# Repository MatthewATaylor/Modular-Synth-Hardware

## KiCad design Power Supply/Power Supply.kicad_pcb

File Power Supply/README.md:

# Power Supply

A linear power supply for +12V, -12V, and +5V.

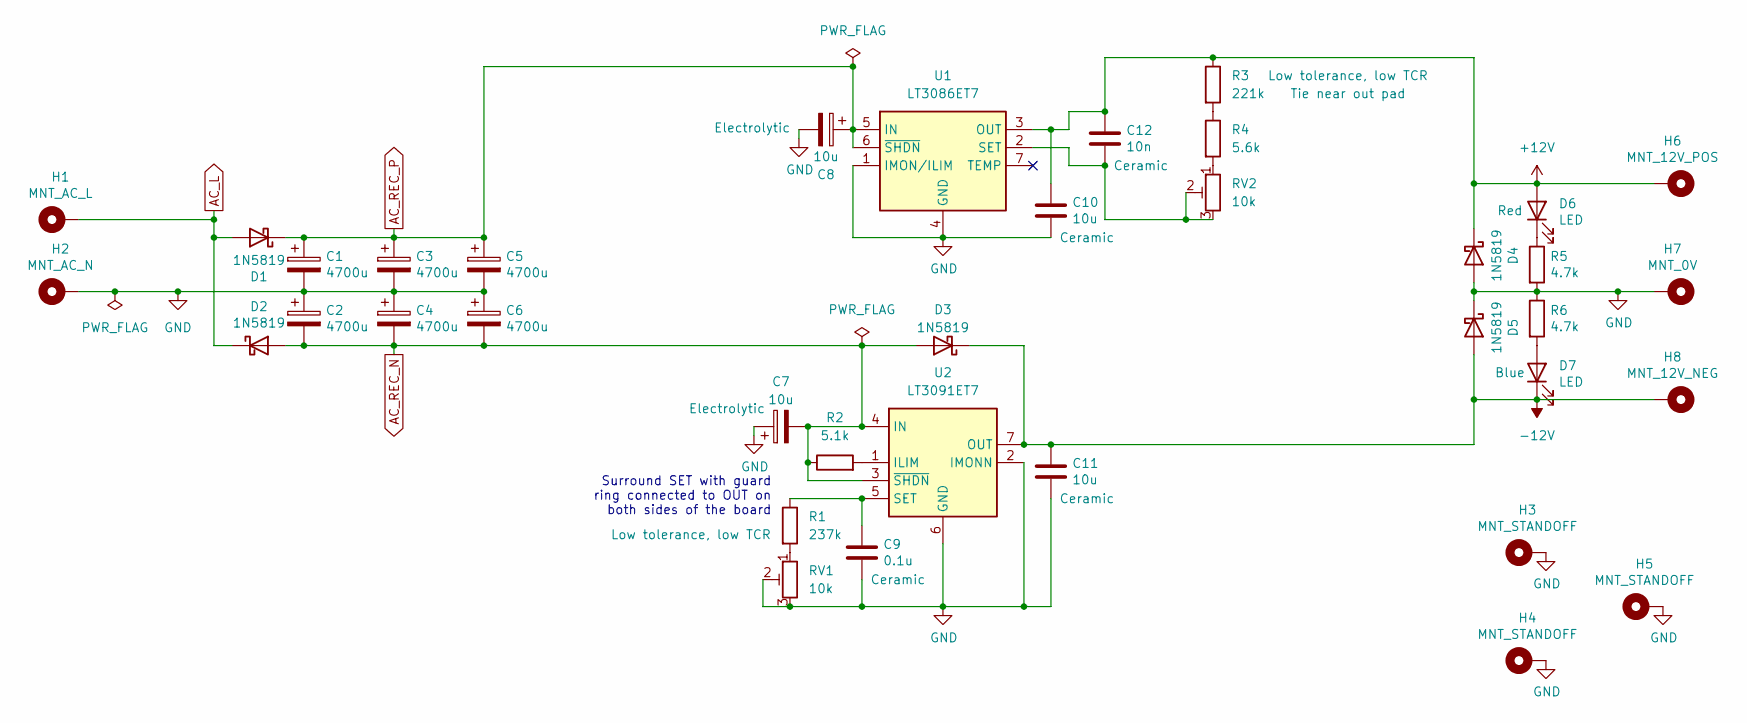
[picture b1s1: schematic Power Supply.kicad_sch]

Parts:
C1, C2, C3, C4, C5, C6: 4700u; CP_Radial_D18.0mm_P7.50mm
C7, C8: 10u; CP_Radial_D5.0mm_P2.50mm
C9: 0.1u; C_Disc_D5.5mm_W2.5mm_P2.50mm
C10, C11: 10u; C_Disc_D5.5mm_W4.0mm_P2.50mm
C12: 10n; C_Disc_D5.5mm_W2.5mm_P2.50mm
D1, D2, D3, D4, D5: 1N5819; D_DO-41_SOD81_P10.16mm_Horizontal
D6, D7: LED; LED_D5.0mm
H1: MNT_AC_L; MountingHole_Pitch1.7mm_Drill1mm
H2: MNT_AC_N; MountingHole_Pitch1.7mm_Drill1mm
H3, H4, H5: MNT_STANDOFF; MountingHole_Pitch7.5mm_Drill3.4mm
H6: MNT_12V_POS; Wuerth_REDCUBE-THR_WP-THRSH_74651195_THR
H7: MNT_0V; Wuerth_REDCUBE-THR_WP-THRSH_74651195_THR
H8: MNT_12V_NEG; Wuerth_REDCUBE-THR_WP-THRSH_74651195_THR
R1: 237k; R_Axial_DIN0207_L6.3mm_D2.5mm_P7.62mm_Horizontal
R2: 5.1k; R_Axial_DIN0207_L6.3mm_D2.5mm_P7.62mm_Horizontal
R3: 221k; R_Axial_DIN0207_L6.3mm_D2.5mm_P7.62mm_Horizontal
R4: 5.6k; R_Axial_DIN0207_L6.3mm_D2.5mm_P7.62mm_Horizontal
R5, R6: 4.7k; R_Axial_DIN0207_L6.3mm_D2.5mm_P7.62mm_Horizontal
RV1, RV2: 10k; Potentiometer_Bourns_3296W_Vertical
U1: LT3086ET7; TO-220-7_P2.54x3.7mm_StaggerOdd_Lead3.8mm_Vertical_HeatSink
U2: LT3091ET7; TO-220-7_P2.54x3.7mm_StaggerOdd_Lead3.8mm_Vertical_HeatSink

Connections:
+12V: C10.1, C12.1, D4.1 (K), D6.2 (A), H6.1, R3.1, U1.3 (OUT)
-12V: C11.1, D3.1 (K), D5.2 (A), D7.1 (K), H8.1, U2.7 (OUT)
AC_L: D1.2 (A), D2.1 (K), H1.1
AC_REC_N: C2.2, C4.2, C6.2, C7.2, D2.2 (A), D3.2 (A), R2.1, U2.3 (~SHDN), U2.4 (IN)
AC_REC_P: C1.1, C3.1, C5.1, C8.1, D1.1 (K), U1.5 (IN), U1.6 (~SHDN)
GND: C1.2, C2.1, C3.2, C4.1, C5.2, C6.1, C7.1, C8.2, C9.2, C10.2, C11.2, D4.2 (A), D5.1 (K), H2.1, H3.1, H4.1, H5.1, H7.1, R5.2, R6.1, RV1.2, RV1.3, U1.1 (IMON/ILIM), U1.4 (GND), U2.2 (IMONN), U2.6 (GND)
unnamed: D6.1 (K), R5.1
unnamed: D7.2 (A), R6.2
unnamed: R1.2, RV1.1
unnamed: R3.2, R4.1
unnamed: R4.2, RV2.1
unnamed: C12.2, RV2.2, RV2.3, U1.2 (SET)
unnamed: R2.2, U2.1 (ILIM)
unnamed: C9.1, R1.1, U2.5 (SET)

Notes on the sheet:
Surround SET with guard ring connected to OUT on both sides of the board

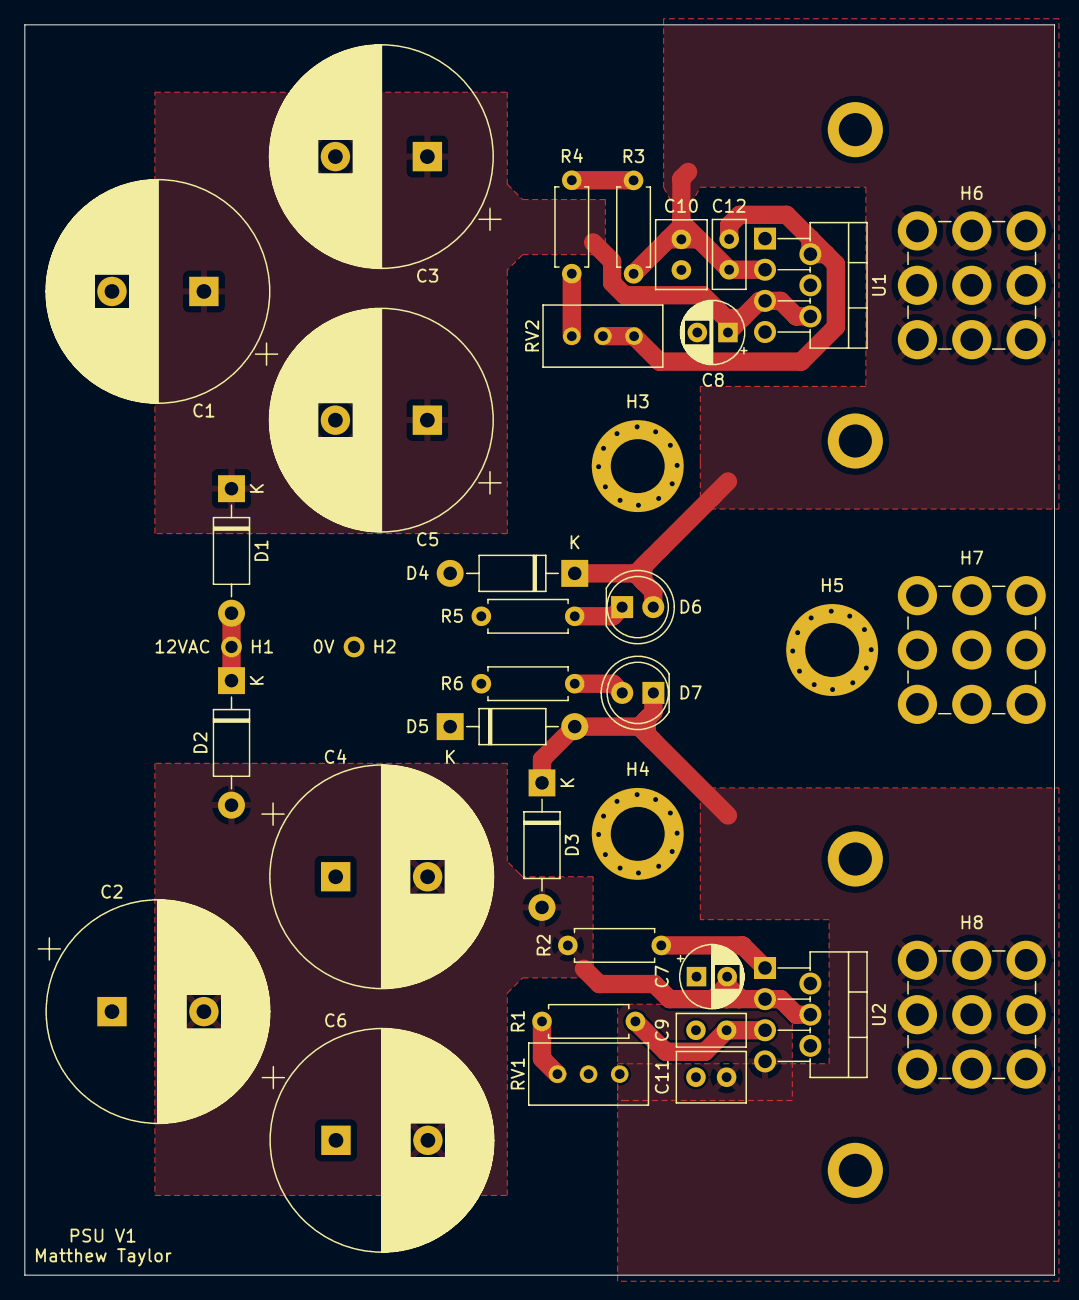
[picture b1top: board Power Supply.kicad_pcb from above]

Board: 2 copper layers, 84.0 x 102.0 mm, 37 parts (0 on the bottom side), 14 nets.

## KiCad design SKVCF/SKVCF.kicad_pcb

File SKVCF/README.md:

# SKVCF

A Sallen-Key voltage-controlled filter, based on [René Schmitz's MS-20-style filter design](https://www.schmitzbits.de/ms20.html), with separate inputs for high- and low-pass filtering.

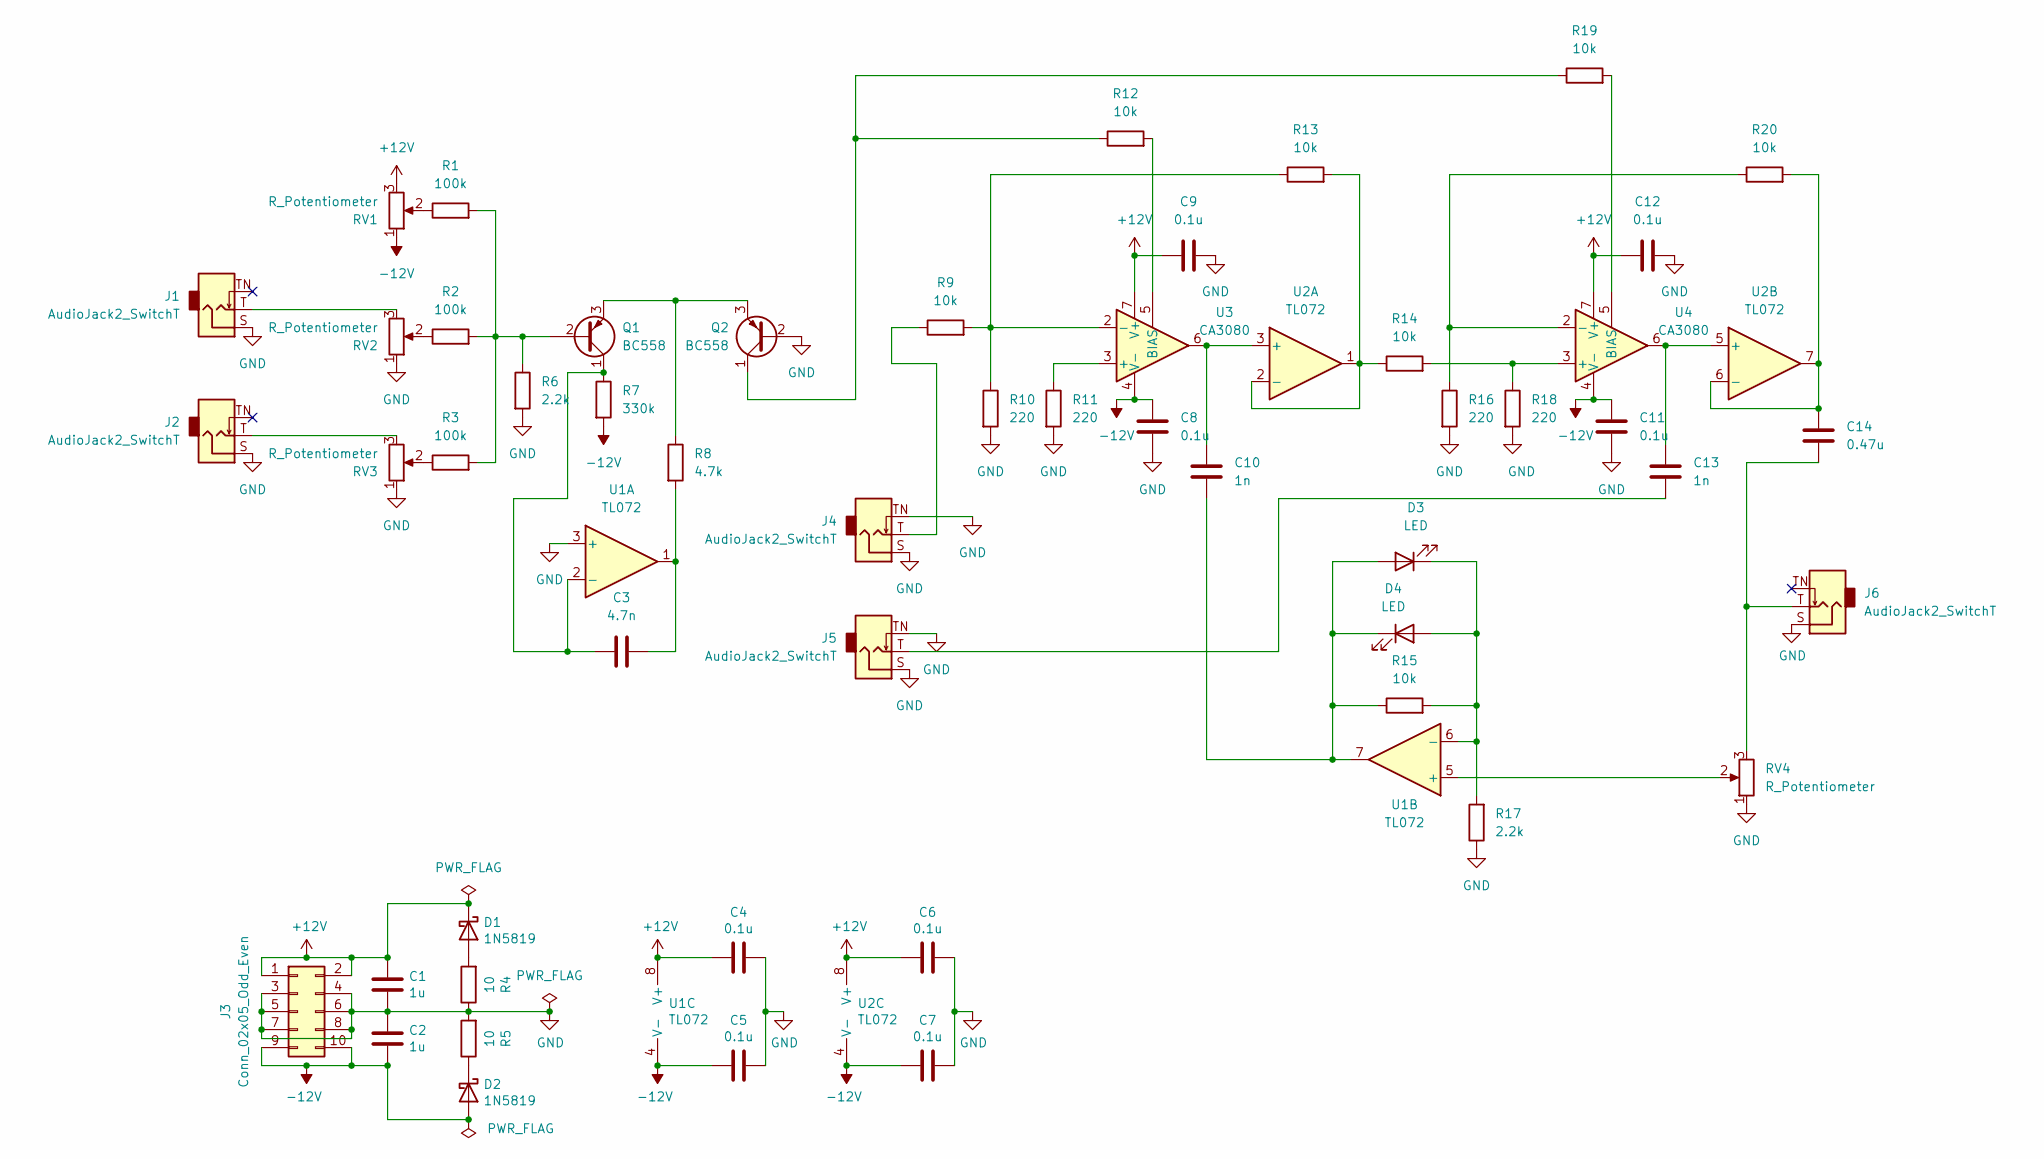
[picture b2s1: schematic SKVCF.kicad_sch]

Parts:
C1, C2: 1u; C_Disc_D5.0mm_W2.5mm_P5.00mm
C3: 4.7n; C_Disc_D5.0mm_W2.5mm_P5.00mm
C4, C5, C6, C7, C8, C9, C11, C12: 0.1u; C_Disc_D5.0mm_W2.5mm_P5.00mm
C10, C13: 1n; C_Disc_D5.0mm_W2.5mm_P5.00mm
C14: 0.47u; C_Disc_D5.0mm_W2.5mm_P5.00mm
D1, D2: 1N5819; D_DO-41_SOD81_P10.16mm_Horizontal
D3, D4: LED; LED_D5.0mm
J1, J2, J4, J5, J6: AudioJack2_SwitchT; Jack_3.5mm_QingPu_WQP-PJ398SM_Vertical_CircularHoles
J3: Conn_02x05_Odd_Even; PinHeader_2x05_P2.54mm_Vertical
Q1, Q2: BC558; TO-92_HandSolder
R1, R2, R3: 100k; R_Axial_DIN0207_L6.3mm_D2.5mm_P7.62mm_Horizontal
R4, R5: 10; R_Axial_DIN0207_L6.3mm_D2.5mm_P7.62mm_Horizontal
R6, R17: 2.2k; R_Axial_DIN0207_L6.3mm_D2.5mm_P7.62mm_Horizontal
R7: 330k; R_Axial_DIN0207_L6.3mm_D2.5mm_P7.62mm_Horizontal
R8: 4.7k; R_Axial_DIN0207_L6.3mm_D2.5mm_P7.62mm_Horizontal
R9, R12, R13, R14, R15, R19, R20: 10k; R_Axial_DIN0207_L6.3mm_D2.5mm_P7.62mm_Horizontal
R10, R11, R16, R18: 220; R_Axial_DIN0207_L6.3mm_D2.5mm_P7.62mm_Horizontal
RV1, RV2, RV3, RV4: R_Potentiometer; Potentiometer_Alpha_RD901F-40-00D_Single_Vertical_CircularH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
U1, U2: TL072; DIP-8_W7.62mm_Socket
U3, U4: CA3080; DIP-8_W7.62mm_Socket

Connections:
+12V: C1.1, C4.1, C6.1, C9.2, C12.2, D1.1 (K), J3.1, J3.2, RV1.3, U1.8 (V+), U2.8 (V+), U3.7 (V+), U4.7 (V+)
-12V: C2.2, C5.1, C7.1, C8.2, C11.2, D2.2 (A), J3.9, J3.10, R7.2, RV1.1, U1.4 (V-), U2.4 (V-), U3.4 (V-), U4.4 (V-)
GND: C1.2, C2.1, C4.2, C5.2, C6.2, C7.2, C8.1, C9.1, C11.1, C12.1, J1.S, J2.S, J3.3, J3.4, J3.5, J3.6, J3.7, J3.8, J4.S, J4.TN, J5.S, J5.TN, J6.S, Q2.2 (B), R4.1, R5.2, R6.2, R10.2, R11.2, R16.2, R17.1, R18.2, RV2.1, RV3.1, RV4.1, U1.3 (+)
unnamed: C3.1, Q1.1 (C), R7.1, U1.2 (-)
unnamed: C3.2, R8.2, U1.1
unnamed: C10.1, U2.3 (+), U3.6
unnamed: C10.2, D3.2 (A), D4.1 (K), R15.1, U1.7
unnamed: C13.1, U2.5 (+), U4.6
unnamed: C13.2, J5.T
unnamed: C14.1, R20.2, U2.6 (-), U2.7
unnamed: C14.2, J6.T, RV4.3
unnamed: D1.2 (A), R4.2
unnamed: D2.1 (K), R5.1
unnamed: D3.1 (K), D4.2 (A), R15.2, R17.2, U1.6 (-)
unnamed: J1.T, RV2.3
unnamed: J2.T, RV3.3
unnamed: J4.T, R9.1
unnamed: Q1.2 (B), R1.2, R2.2, R3.2, R6.1
unnamed: Q1.3 (E), Q2.3 (E), R8.1
unnamed: Q2.1 (C), R12.1, R19.1
unnamed: R1.1, RV1.2
unnamed: R2.1, RV2.2
unnamed: R3.1, RV3.2
unnamed: R9.2, R10.1, R13.1, U3.2 (-)
unnamed: R11.1, U3.3 (+)
unnamed: R12.2, U3.5 (BIAS)
unnamed: R13.2, R14.1, U2.1, U2.2 (-)
unnamed: R14.2, R18.1, U4.3 (+)
unnamed: R16.1, R20.1, U4.2 (-)
unnamed: R19.2, U4.5 (BIAS)
unnamed: RV4.2, U1.5 (+)

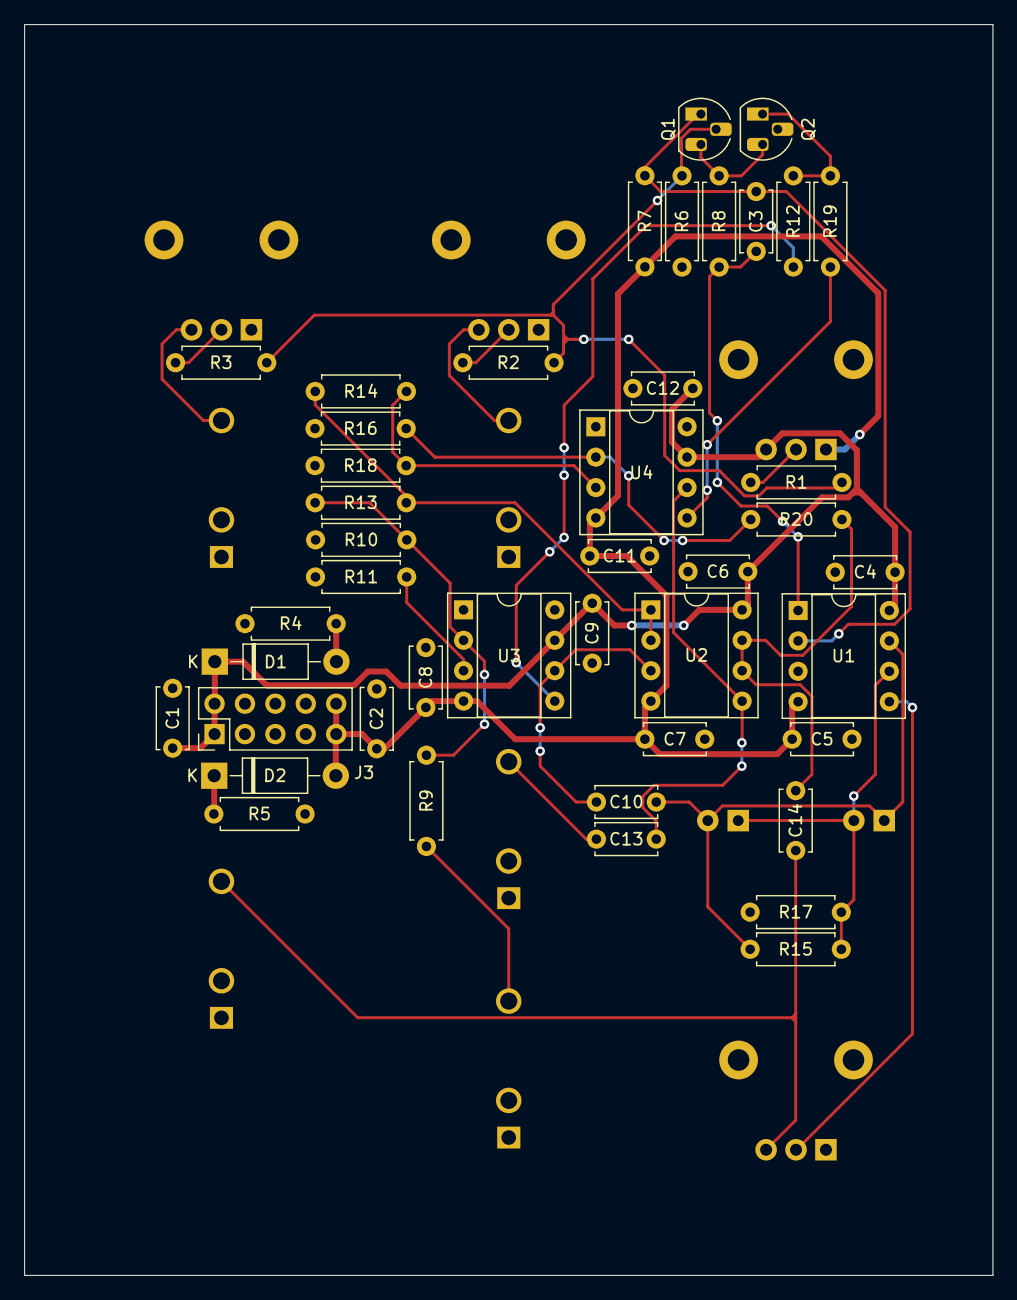
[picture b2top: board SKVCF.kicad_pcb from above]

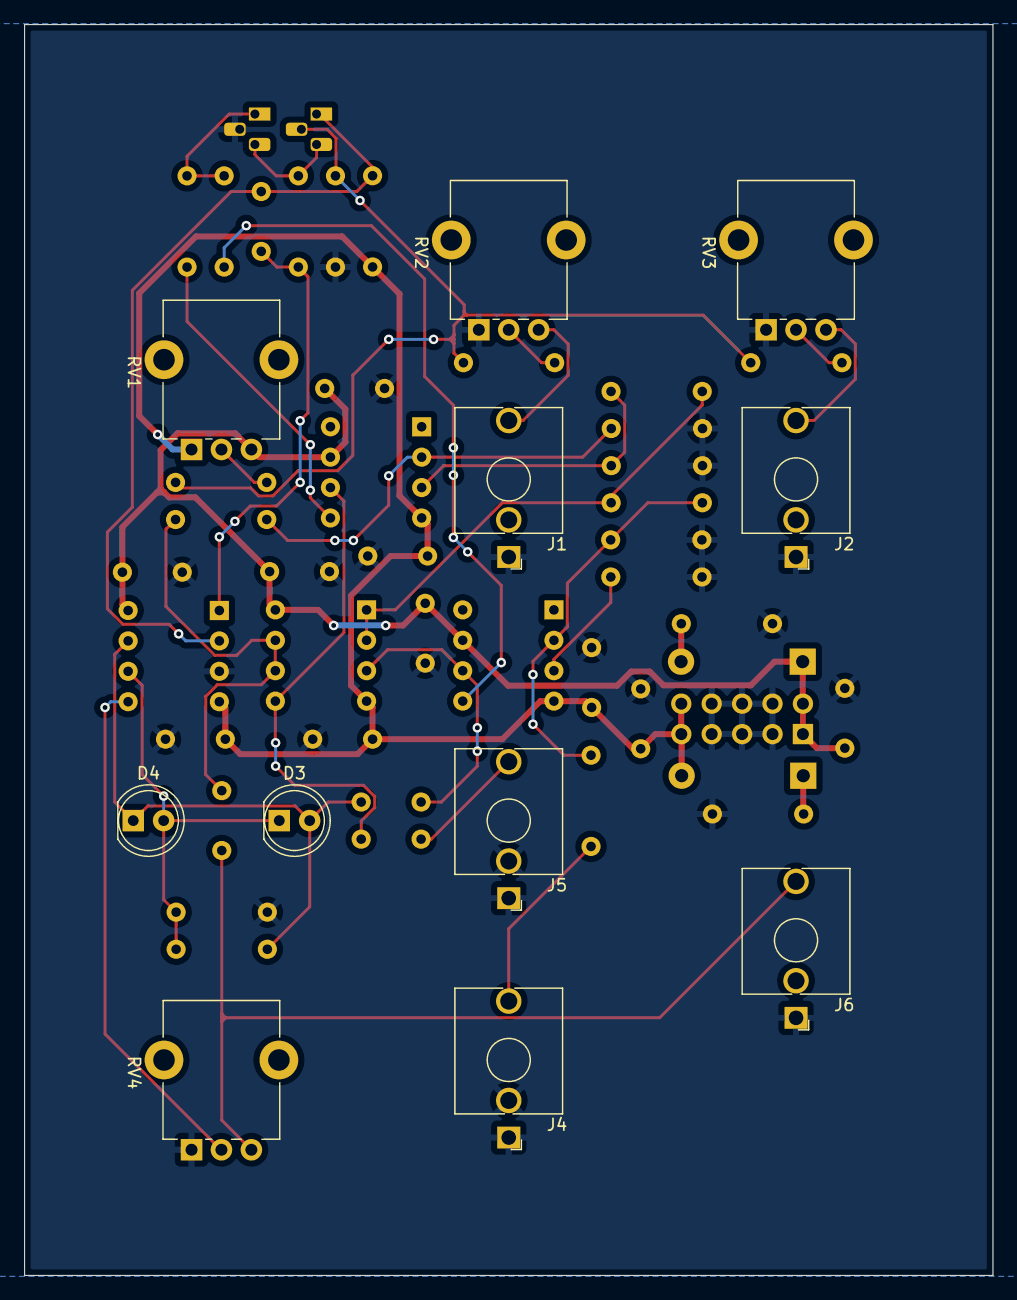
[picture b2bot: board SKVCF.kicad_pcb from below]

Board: 2 copper layers, 80.9 x 104.5 mm, 54 parts (11 on the bottom side), 31 nets.

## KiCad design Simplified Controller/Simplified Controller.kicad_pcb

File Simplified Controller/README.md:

# Simplified Controller

A modified version of [Controller](https://github.com/MatthewATaylor/Modular-Synth-Hardware/tree/main/Controller), with the sequencer removed (i.e. just an 8 channel USB MIDI to CV converter).

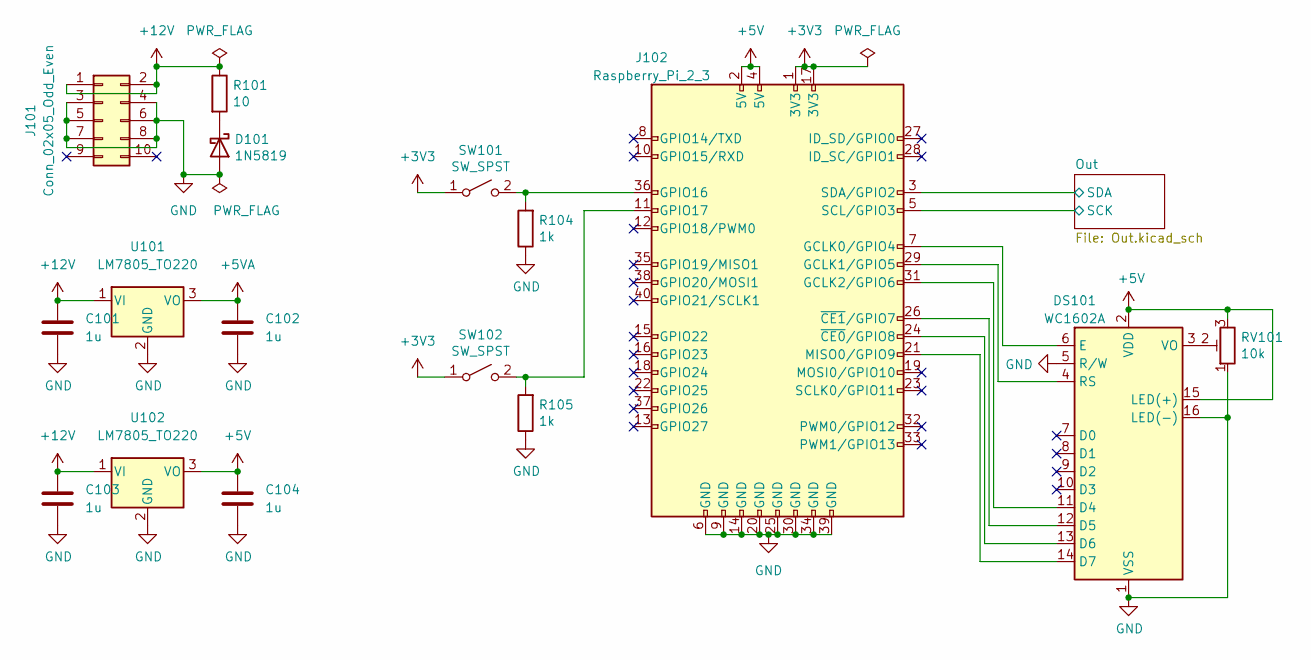
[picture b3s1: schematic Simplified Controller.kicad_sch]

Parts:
C101, C102, C103, C104: 1u; C_Disc_D5.0mm_W2.5mm_P5.00mm
D101: 1N5819; D_DO-41_SOD81_P10.16mm_Horizontal
DS101: WC1602A; WC1602A_Outline
J101: Conn_02x05_Odd_Even; PinHeader_2x05_P2.54mm_Vertical
J102: Raspberry_Pi_2_3; Raspberry_Pi_Zero_Socketed_THT_FaceDown
R101: 10; R_Axial_DIN0207_L6.3mm_D2.5mm_P7.62mm_Horizontal
R104, R105: 1k; R_Axial_DIN0207_L6.3mm_D2.5mm_P7.62mm_Horizontal
RV101: 10k; Potentiometer_Runtron_RM-065_Vertical
SW101, SW102: SW_SPST; PBS-105
U101, U102: LM7805_TO220; TO-220-3_Vertical

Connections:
+3V3: J102.1 (3V3), J102.17 (3V3), SW101.1 (A), SW102.1 (A)
+5V: C104.1, DS101.2 (VDD), DS101.15 (LED(+)), J102.2 (5V), J102.4 (5V), RV101.3, U102.3 (VO); also elsewhere on the board
+5VA: C102.1, U101.3 (VO); also elsewhere on the board
+12V: C101.1, C103.1, J101.1, J101.2, R101.1, U101.1 (VI), U102.1 (VI)
/Out/SCK: J102.5 (SCL/GPIO3); also elsewhere on the board
/Out/SDA: J102.3 (SDA/GPIO2); also elsewhere on the board
GND: C101.2, C102.2, C103.2, C104.2, D101.2 (A), DS101.1 (VSS), DS101.5 (R/W), DS101.16 (LED(-)), J101.3, J101.4, J101.5, J101.6, J101.7, J101.8, J102.6 (GND), J102.9 (GND), J102.14 (GND), J102.20 (GND), J102.25 (GND), J102.30 (GND), J102.34 (GND), J102.39 (GND), R104.1, R105.1, RV101.1, U101.2 (GND), U102.2 (GND); also elsewhere on the board
unnamed: D101.1 (K), R101.2
unnamed: DS101.3 (VO), RV101.2
unnamed: DS101.4 (RS), J102.29 (GCLK1/GPIO5)
unnamed: DS101.6 (E), J102.7 (GCLK0/GPIO4)
unnamed: DS101.11 (D4), J102.31 (GCLK2/GPIO6)
unnamed: DS101.12 (D5), J102.26 (~CE1/GPIO7)
unnamed: DS101.13 (D6), J102.24 (~CE0/GPIO8)
unnamed: DS101.14 (D7), J102.21 (MISO0/GPIO9)
unnamed: J102.11 (GPIO17), R105.2, SW102.2 (B)
unnamed: J102.36 (GPIO16), R104.2, SW101.2 (B)

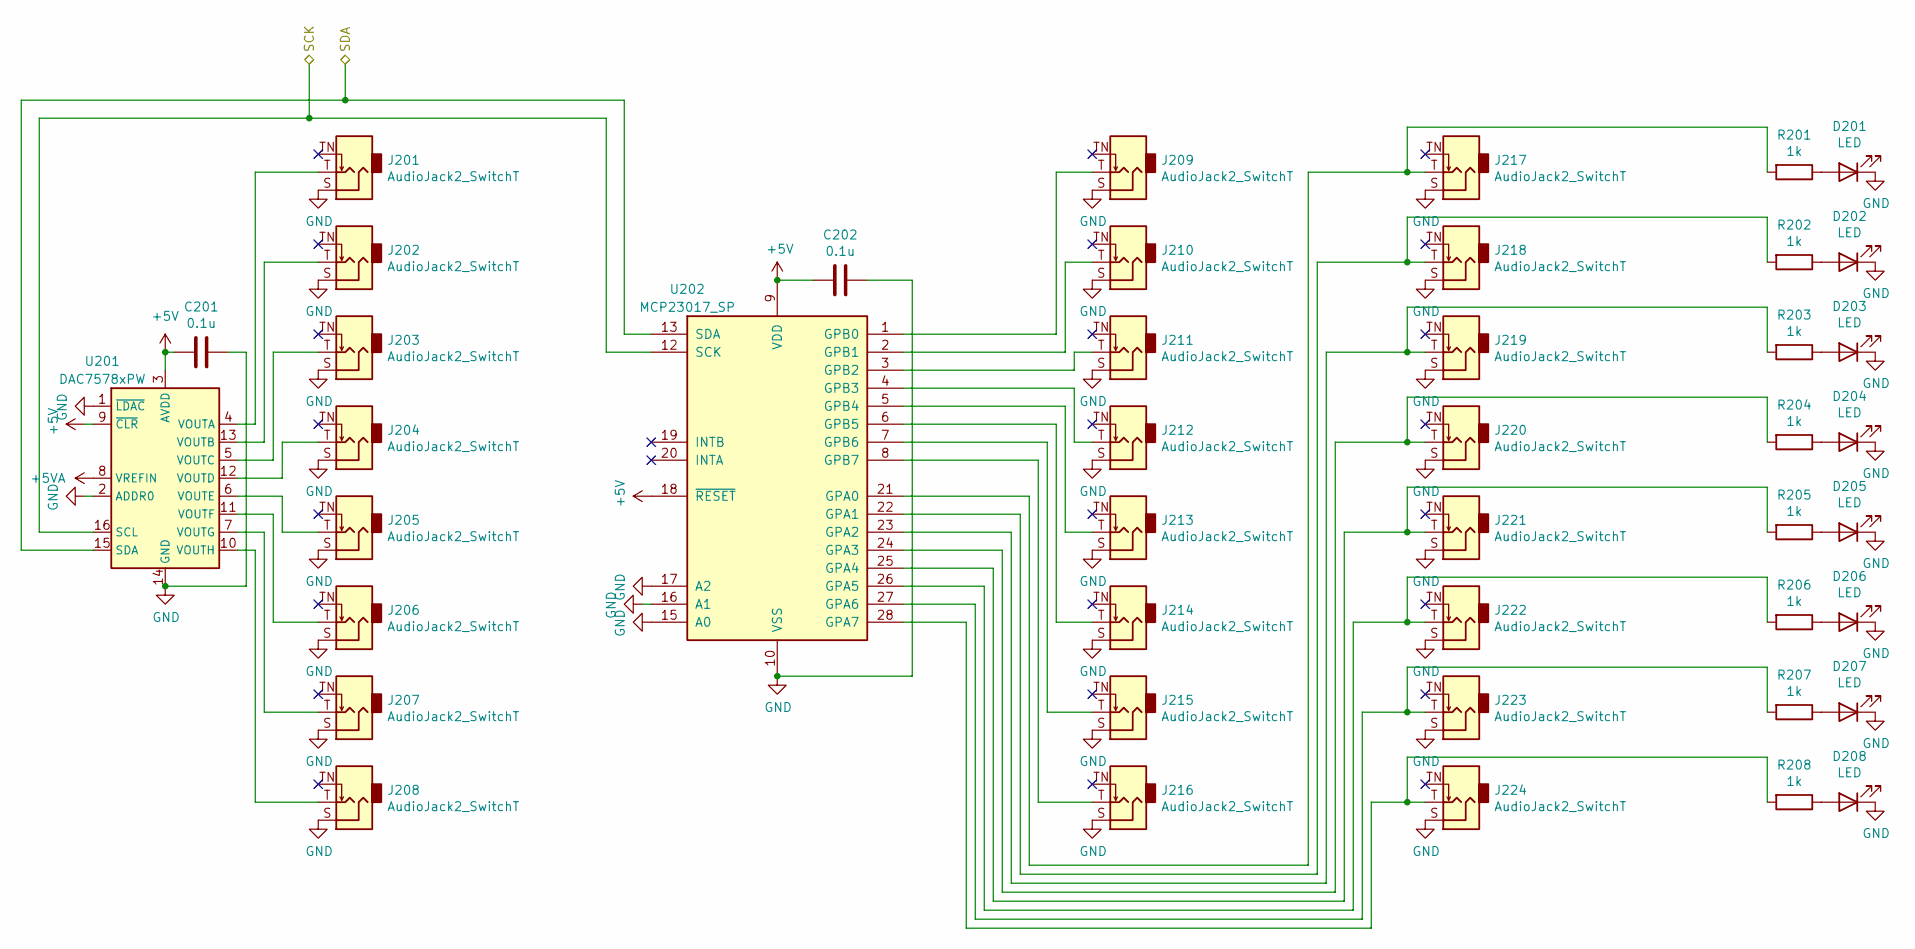
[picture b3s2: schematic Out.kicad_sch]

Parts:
C201, C202: 0.1u; C_Disc_D5.0mm_W2.5mm_P5.00mm
D201, D202, D203, D204, D205, D206, D207, D208: LED; LED_D5.0mm
J201, J202, J203, J204, J205, J206, J207, J208, J209, J210, J211, J212, J213, J214, J215, J216, J217, J218, J219, J220, J221, J222, J223, J224: AudioJack2_SwitchT; Jack_3.5mm_QingPu_WQP-PJ398SM_Vertical_CircularHoles
R201, R202, R203, R204, R205, R206, R207, R208: 1k; R_Axial_DIN0207_L6.3mm_D2.5mm_P7.62mm_Horizontal
U201: DAC7578xPW; TSSOP-16_4.4x5mm_P0.65mm
U202: MCP23017_SP; DIP-28_W7.62mm_Socket

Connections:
+5V: C201.2, C202.2, U201.3 (AVDD), U201.9 (~CLR), U202.9 (VDD), U202.18 (~RESET); also elsewhere on the board
+5VA: U201.8 (VREFIN); also elsewhere on the board
/Out/SCK: U201.16 (SCL), U202.12 (SCK); also elsewhere on the board
/Out/SDA: U201.15 (SDA), U202.13 (SDA); also elsewhere on the board
GND: C201.1, C202.1, D201.1 (K), D202.1 (K), D203.1 (K), D204.1 (K), D205.1 (K), D206.1 (K), D207.1 (K), D208.1 (K), J201.S, J202.S, J203.S, J204.S, J205.S, J206.S, J207.S, J208.S, J209.S, J210.S, J211.S, J212.S, J213.S, J214.S, J215.S, J216.S, J217.S, J218.S, J219.S, J220.S, J221.S, J222.S, J223.S, J224.S, U201.1 (~LDAC), U201.2 (ADDR0), U201.14 (GND), U202.10 (VSS), U202.15 (A0), U202.16 (A1), U202.17 (A2); also elsewhere on the board
unnamed: D201.2 (A), R201.1
unnamed: D202.2 (A), R202.1
unnamed: D203.2 (A), R203.1
unnamed: D204.2 (A), R204.1
unnamed: D205.2 (A), R205.1
unnamed: D206.2 (A), R206.1
unnamed: D207.2 (A), R207.1
unnamed: D208.2 (A), R208.1
unnamed: J201.T, U201.4 (VOUTA)
unnamed: J202.T, U201.13 (VOUTB)
unnamed: J203.T, U201.5 (VOUTC)
unnamed: J204.T, U201.12 (VOUTD)
unnamed: J205.T, U201.6 (VOUTE)
unnamed: J206.T, U201.11 (VOUTF)
unnamed: J207.T, U201.7 (VOUTG)
unnamed: J208.T, U201.10 (VOUTH)
unnamed: J209.T, U202.1 (GPB0)
unnamed: J210.T, U202.2 (GPB1)
unnamed: J211.T, U202.3 (GPB2)
unnamed: J212.T, U202.4 (GPB3)
unnamed: J213.T, U202.5 (GPB4)
unnamed: J214.T, U202.6 (GPB5)
unnamed: J215.T, U202.7 (GPB6)
unnamed: J216.T, U202.8 (GPB7)
unnamed: J217.T, R201.2, U202.21 (GPA0)
unnamed: J218.T, R202.2, U202.22 (GPA1)
unnamed: J219.T, R203.2, U202.23 (GPA2)
unnamed: J220.T, R204.2, U202.24 (GPA3)
unnamed: J221.T, R205.2, U202.25 (GPA4)
unnamed: J222.T, R206.2, U202.26 (GPA5)
unnamed: J223.T, R207.2, U202.27 (GPA6)
unnamed: J224.T, R208.2, U202.28 (GPA7)

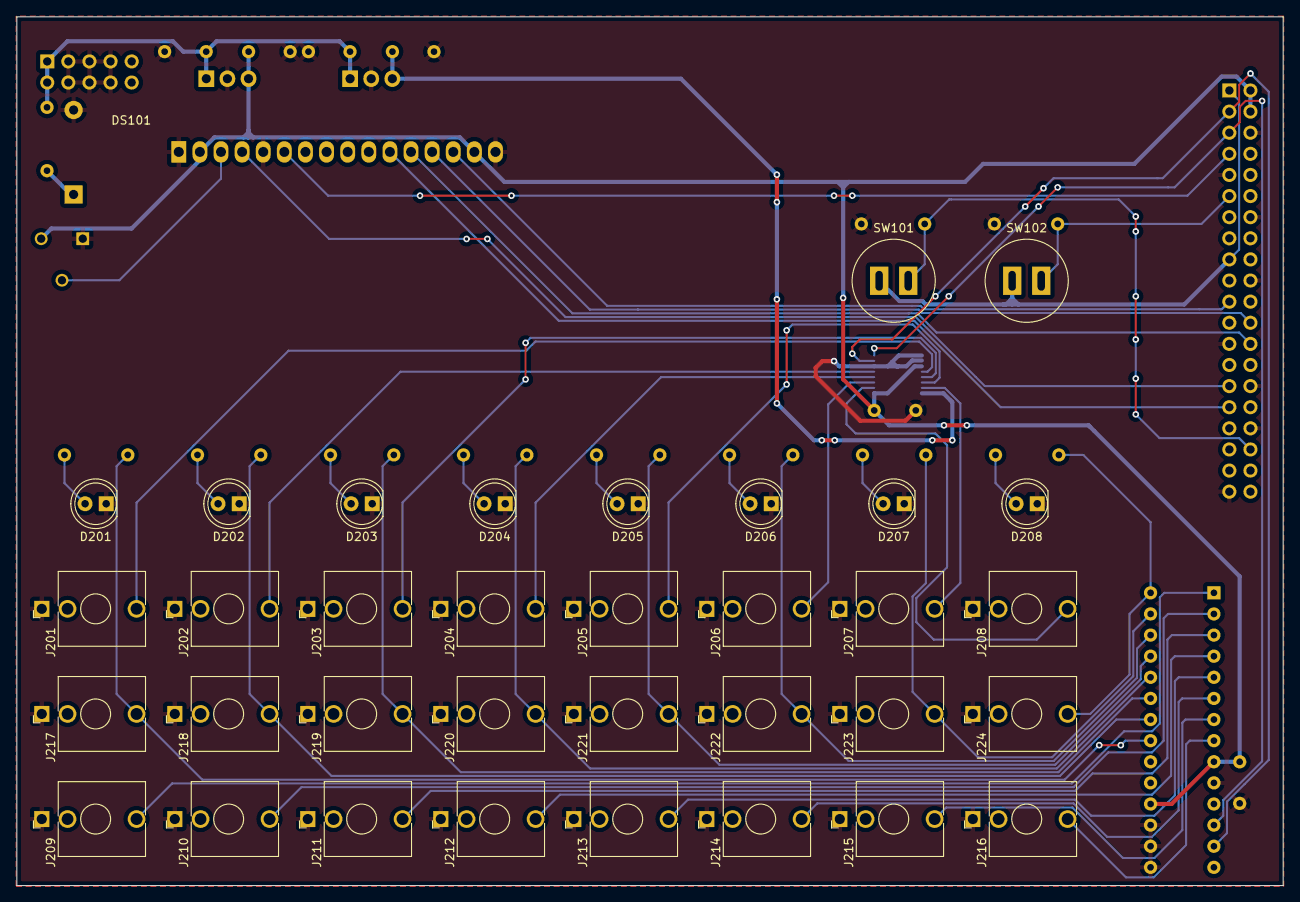
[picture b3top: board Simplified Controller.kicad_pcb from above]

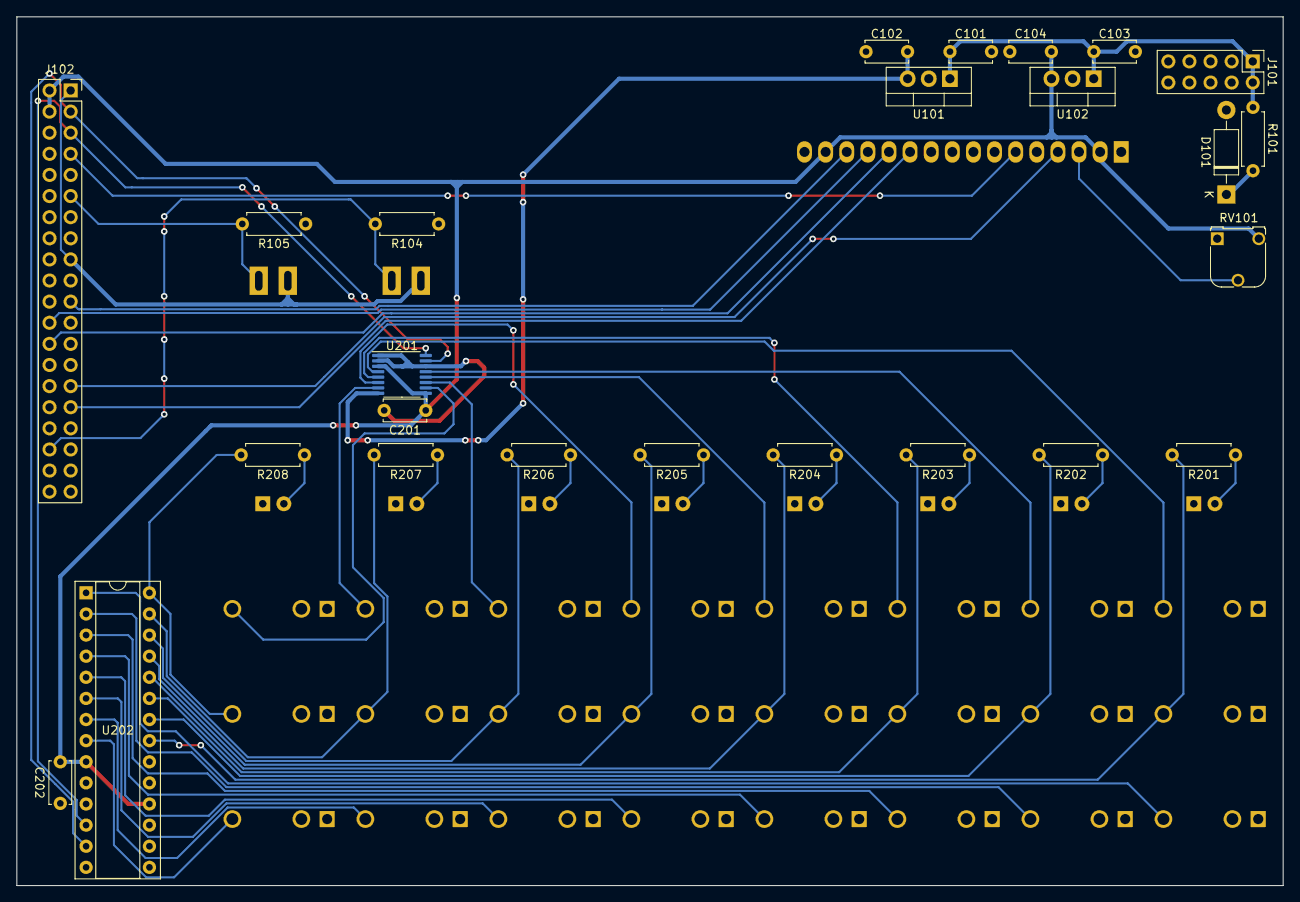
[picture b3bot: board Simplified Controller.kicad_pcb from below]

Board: 2 copper layers, 152.3 x 104.5 mm, 60 parts (25 on the bottom side), 49 nets.

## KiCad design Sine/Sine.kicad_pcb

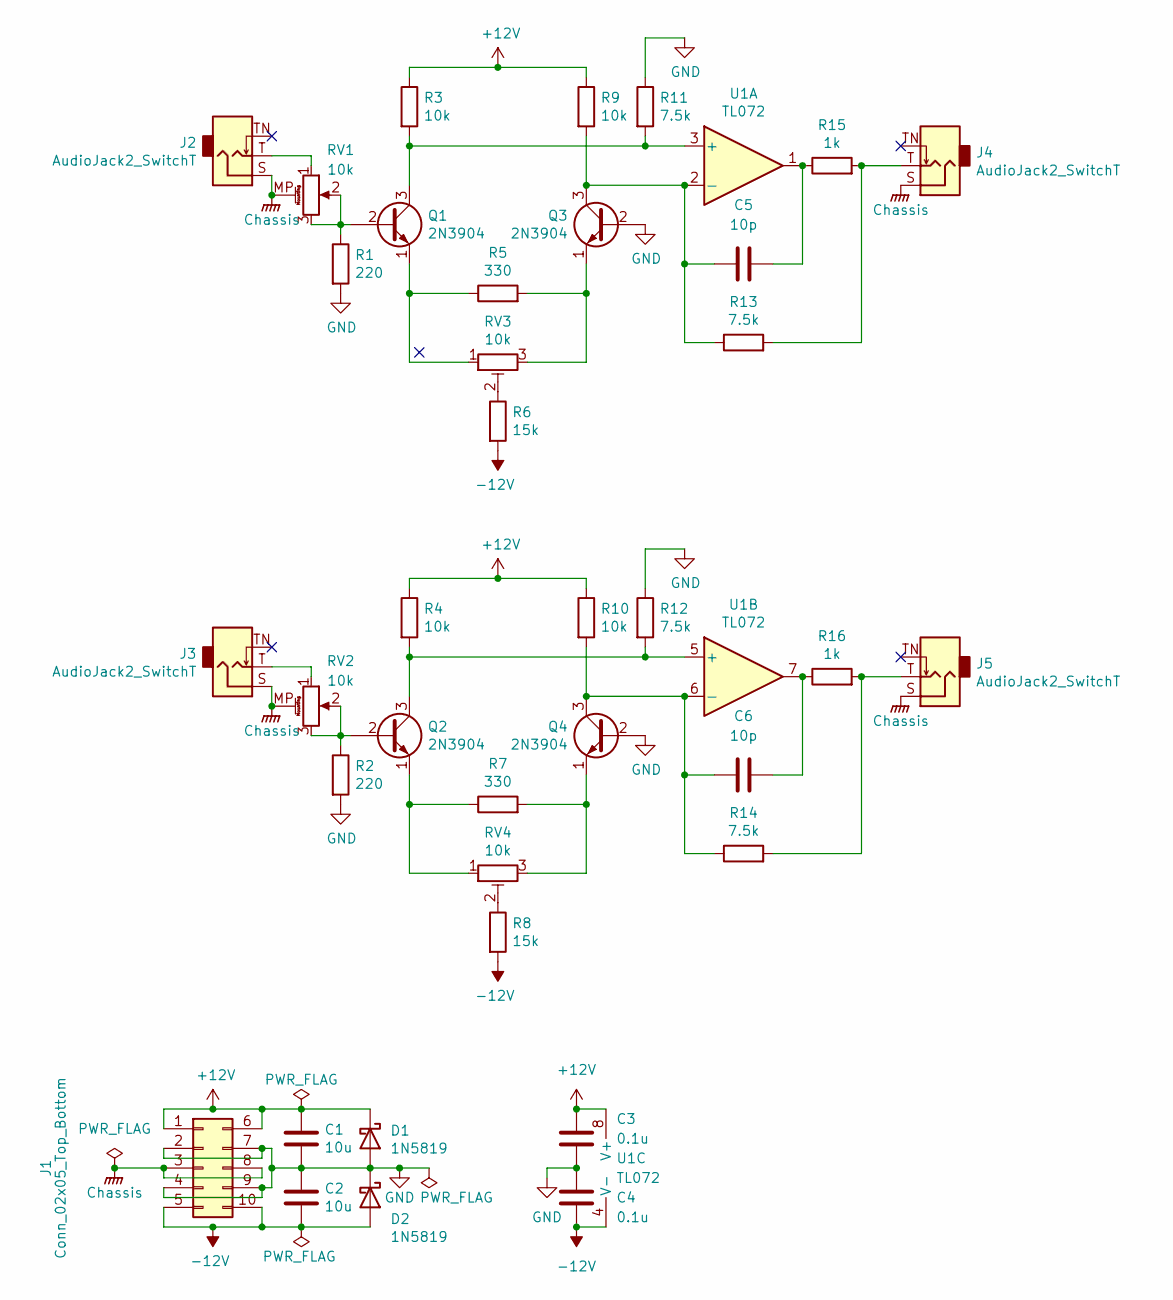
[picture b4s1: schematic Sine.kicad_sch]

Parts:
C1, C2: 10u; C_Disc_D5.5mm_W4.0mm_P2.50mm
C3, C4: 0.1u; C_Disc_D5.5mm_W2.5mm_P2.50mm
C5, C6: 10p; C_Disc_D5.5mm_W2.5mm_P2.50mm
D1, D2: 1N5819; D_DO-41_SOD81_P10.16mm_Horizontal
J1: Conn_02x05_Top_Bottom; Molex_Mini-Fit_Jr_5566-10A_2x05_P4.20mm_Vertical
J2, J3, J4, J5: AudioJack2_SwitchT; Jack_3.5mm_QingPu_WQP-PJ398SM_Vertical_CircularHoles
Q1, Q2, Q3, Q4: 2N3904; TO-92_HandSolder
R1, R2: 220; R_Axial_DIN0207_L6.3mm_D2.5mm_P7.62mm_Horizontal
R3, R4, R9, R10: 10k; R_Axial_DIN0207_L6.3mm_D2.5mm_P7.62mm_Horizontal
R5, R7: 330; R_Axial_DIN0207_L6.3mm_D2.5mm_P7.62mm_Horizontal
R6, R8: 15k; R_Axial_DIN0207_L6.3mm_D2.5mm_P7.62mm_Horizontal
R11, R12, R13, R14: 7.5k; R_Axial_DIN0207_L6.3mm_D2.5mm_P7.62mm_Horizontal
R15, R16: 1k; R_Axial_DIN0207_L6.3mm_D2.5mm_P7.62mm_Horizontal
RV1, RV2: 10k; Potentiometer_Alpha_RD901F-40-00D_Single_Vertical_MP
RV3, RV4: 10k; Potentiometer_Runtron_RM-065_Vertical
U1: TL072; DIP-8_W7.62mm_Socket

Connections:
+12V: C1.1, C3.2, D1.1 (K), J1.1, J1.6, R3.1, R4.1, R9.1, R10.1, U1.8 (V+)
-12V: C2.2, C4.1, D2.2 (A), J1.5, J1.10, R6.2, R8.2, U1.4 (V-)
Chassis: J1.3, J1.8, J2.S, J3.S, J4.S, J5.S, RV1.MP (MountPin), RV2.MP (MountPin)
GND: C1.2, C2.1, C3.1, C4.2, D1.2 (A), D2.1 (K), J1.2, J1.4, J1.7, J1.9, Q3.2 (B), Q4.2 (B), R1.2, R2.2, R11.1, R12.1
unnamed: C5.1, R15.1, U1.1
unnamed: C6.1, R16.1, U1.7
unnamed: J2.T, RV1.1
unnamed: J3.T, RV2.1
unnamed: J4.T, R13.2, R15.2
unnamed: J5.T, R14.2, R16.2
unnamed: Q1.2 (B), R1.1, RV1.2, RV1.3
unnamed: Q1.3 (C), R3.2, R11.2, U1.3 (+)
unnamed: Q1.1 (E), R5.1, RV3.1
unnamed: Q2.2 (B), R2.1, RV2.2, RV2.3
unnamed: Q2.3 (C), R4.2, R12.2, U1.5 (+)
unnamed: Q2.1 (E), R7.1, RV4.1
unnamed: C5.2, Q3.3 (C), R9.2, R13.1, U1.2 (-)
unnamed: Q3.1 (E), R5.2, RV3.3
unnamed: C6.2, Q4.3 (C), R10.2, R14.1, U1.6 (-)
unnamed: Q4.1 (E), R7.2, RV4.3
unnamed: R6.1, RV3.2
unnamed: R8.1, RV4.2

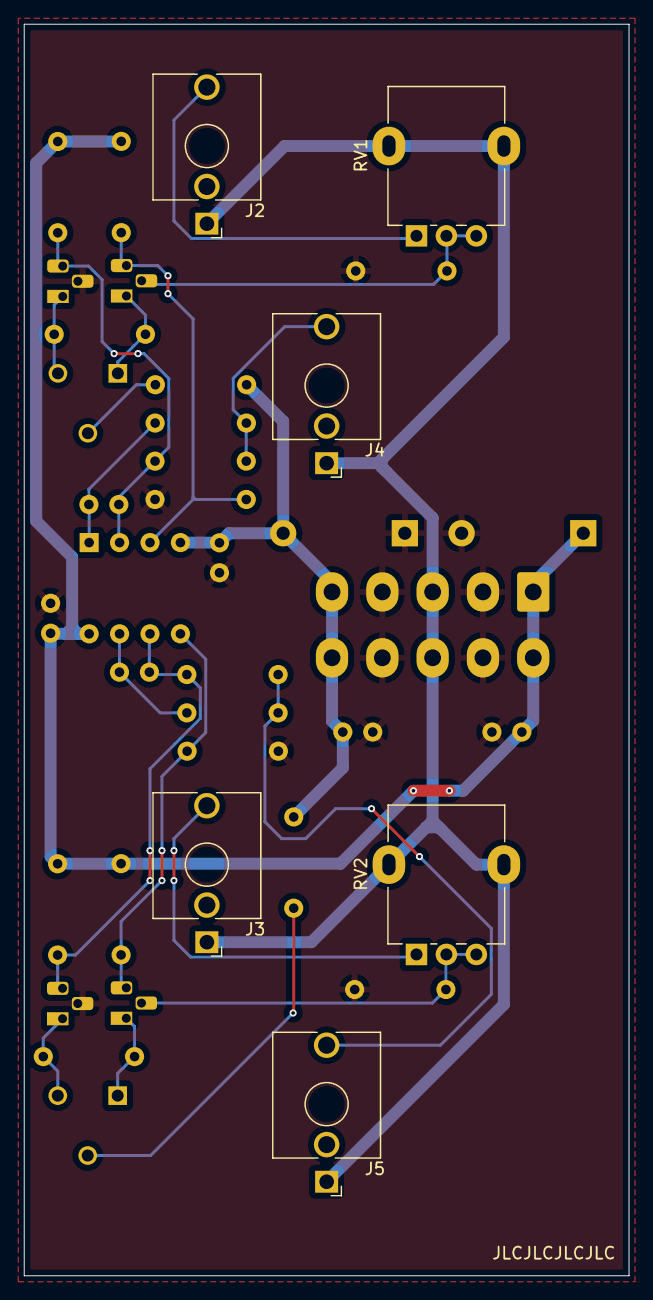
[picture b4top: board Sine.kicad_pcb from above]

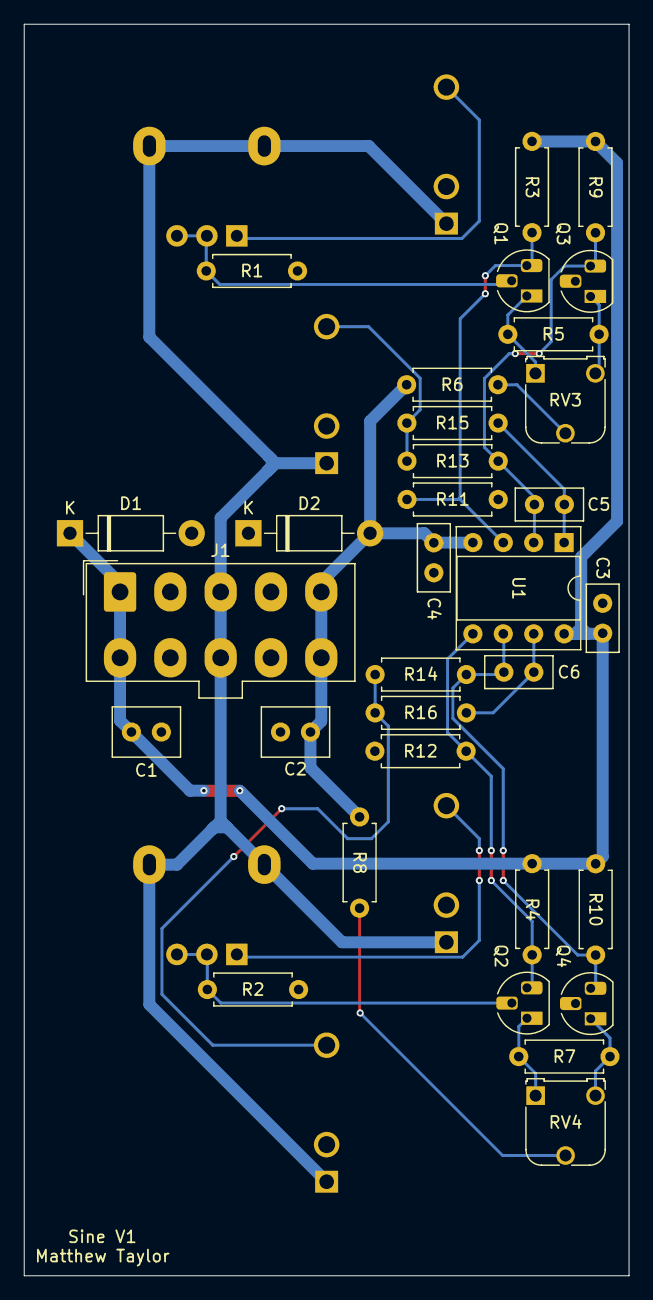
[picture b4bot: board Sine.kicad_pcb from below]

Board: 2 copper layers, 50.5 x 104.5 mm, 38 parts (32 on the bottom side), 22 nets.
